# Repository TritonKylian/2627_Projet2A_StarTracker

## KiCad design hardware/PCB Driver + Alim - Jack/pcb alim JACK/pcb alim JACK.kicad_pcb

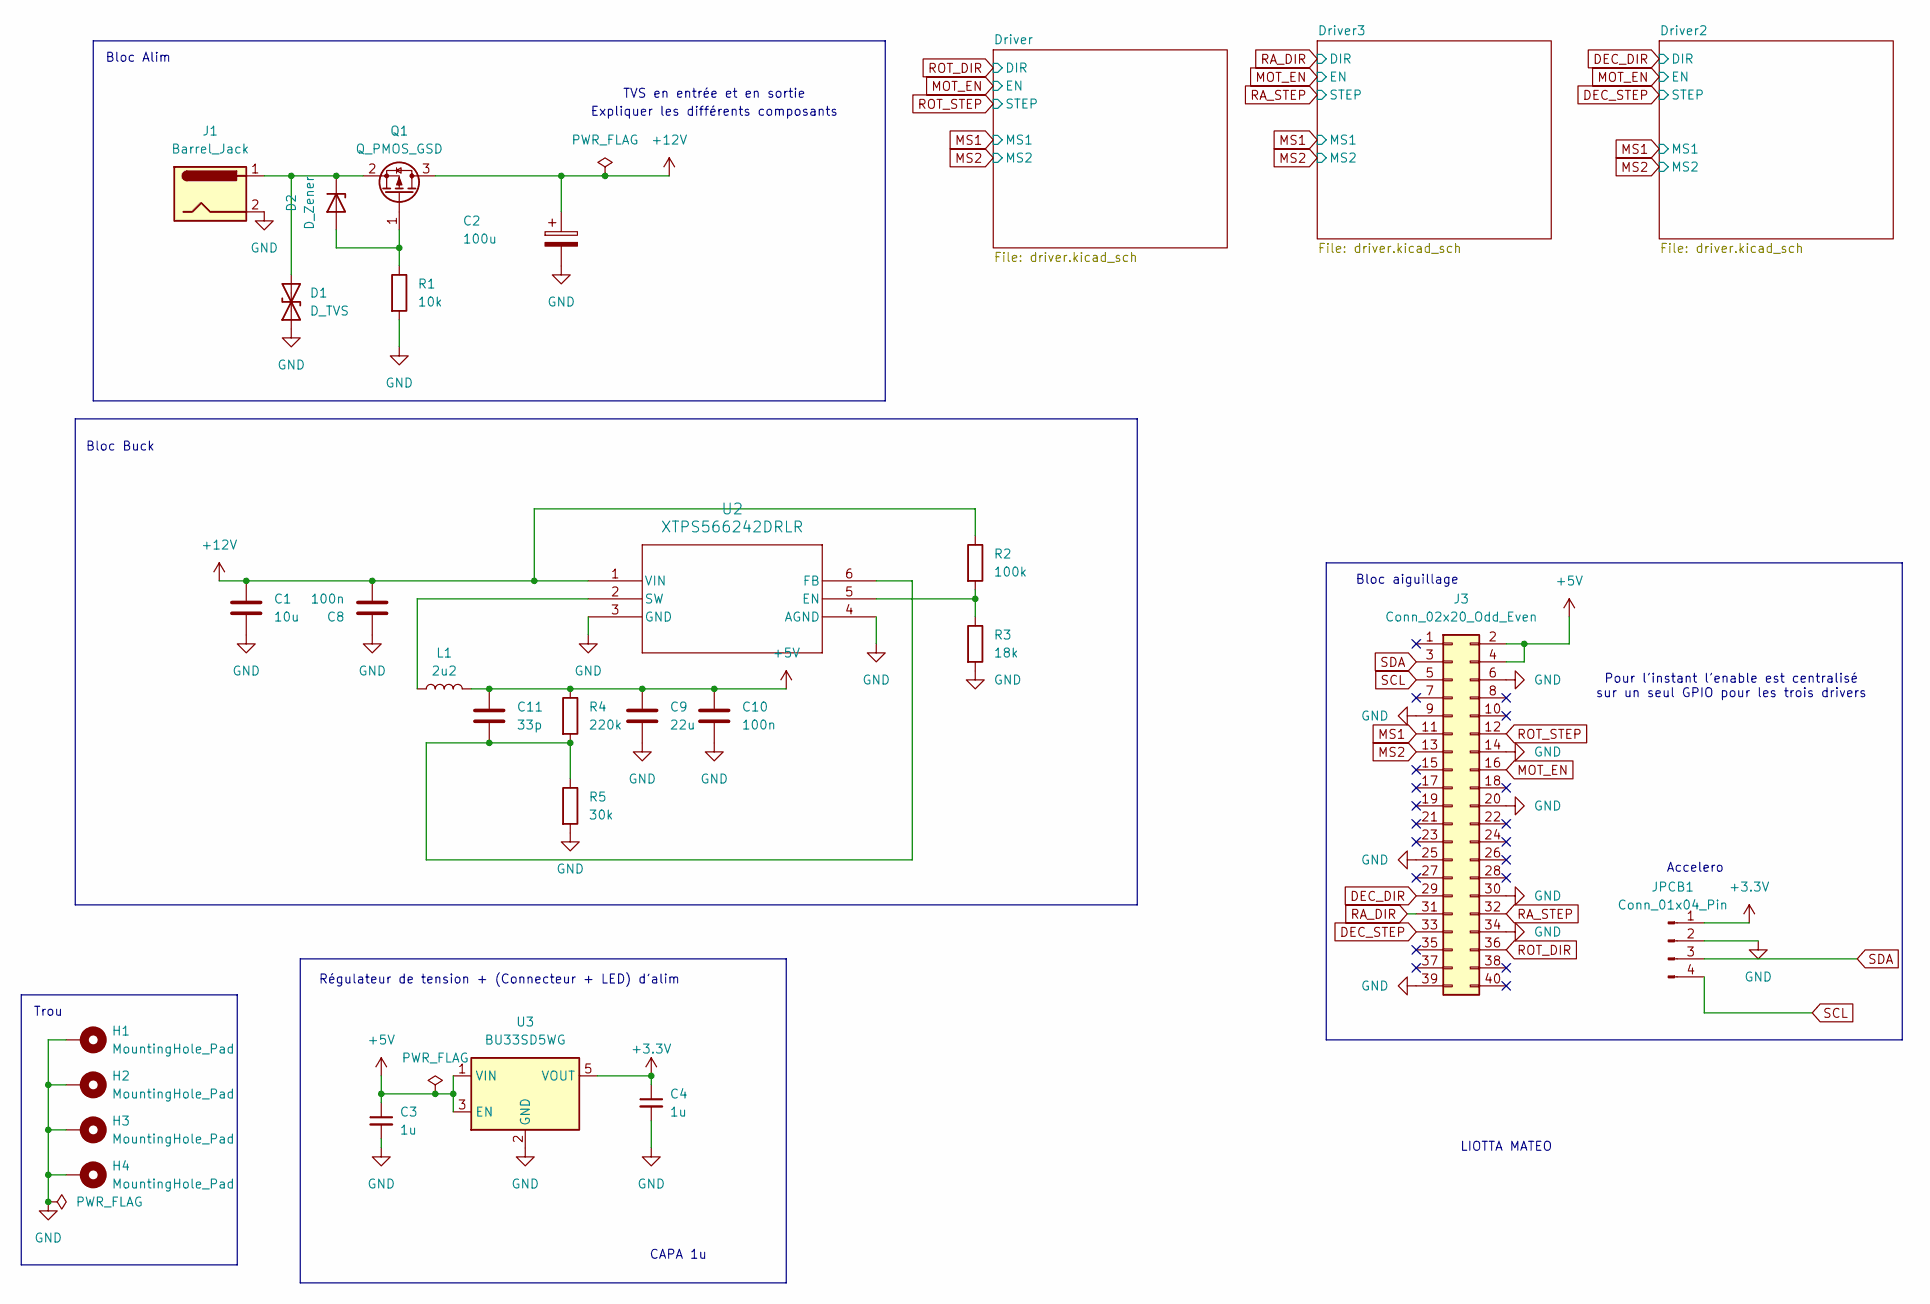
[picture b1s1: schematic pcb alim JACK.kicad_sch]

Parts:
C1: 10u; C_0805_2012Metric
C2: 100u; CP_Elec_6.3x7.7
C3, C4: 1u; C_0805_2012Metric_Pad1.18x1.45mm_HandSolder
C8, C10: 100n; C_0603_1608Metric
C9: 22u; C_0805_2012Metric
C11: 33p; C_0603_1608Metric
D1: D_TVS; D_SMB
D2: D_Zener; D_DO-35_SOD27_P7.62mm_Horizontal
H1, H2, H3, H4: MountingHole_Pad; MountingHole_2.7mm_M2.5_Pad
J1: Barrel_Jack; BarrelJack_CUI_PJ-102AH_Horizontal
J3: Conn_02x20_Odd_Even; PinSocket_2x20_P2.54mm_Vertical
JPCB1: Conn_01x04_Pin; PinHeader_1x04_P2.54mm_Vertical
L1: 2u2; L_Wuerth_WE-PD-Typ-7345; MPN 744777002
Q1: Q_PMOS_GSD; TO-263-2
R1: 10k; R_1206_3216Metric_Pad1.30x1.75mm_HandSolder
R2: 100k; R_0603_1608Metric
R3: 18k; R_0603_1608Metric
R4: 220k; R_0603_1608Metric
R5: 30k; R_0603_1608Metric
U2: XTPS566242DRLR; SOT-563
U3: BU33SD5WG; SOT-23-5

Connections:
+3.3V: C4.1, JPCB1.1, U3.5 (VOUT); also elsewhere on the board
+5V: C3.1, C9.1, C10.1, C11.1, J3.2, J3.4, L1.2, R4.1, U3.1 (VIN), U3.3 (EN)
+12V: C1.1, C2.1, C8.1, Q1.3 (D), R2.1, U2.1 (VIN); also elsewhere on the board
DEC_DIR: J3.29; also elsewhere on the board
DEC_STEP: J3.33; also elsewhere on the board
GND: C1.2, C2.2, C3.2, C4.2, C8.2, C9.2, C10.2, D1.1 (A1), H1.1 (1_1), H2.1 (1_1), H3.1 (1_1), H4.1 (1_1), J1.2, J3.6, J3.9, J3.14, J3.20, J3.25, J3.30, J3.34, J3.39, JPCB1.2, R1.2, R3.2, R5.2, U2.3 (GND), U2.4 (AGND), U3.2 (GND); also elsewhere on the board
MOT_EN: J3.16; also elsewhere on the board
MS1: J3.11; also elsewhere on the board
MS2: J3.13; also elsewhere on the board
unnamed: D1.2 (A2), D2.1 (K), J1.1, Q1.2 (S)
unnamed: D2.2 (A), Q1.1 (G), R1.1
unnamed: R2.2, R3.1, U2.5 (EN)
unnamed: C11.2, R4.2, R5.1, U2.6 (FB)
unnamed: L1.1, U2.2 (SW)
RA_DIR: J3.31; also elsewhere on the board
RA_STEP: J3.32; also elsewhere on the board
ROT_DIR: J3.36; also elsewhere on the board
ROT_STEP: J3.12; also elsewhere on the board
SCL: J3.5, JPCB1.4
SDA: J3.3, JPCB1.3

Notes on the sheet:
CAPA 1u
Accelero
Pour l'instant l'enable est centralisé sur un seul GPIO pour les trois drivers
Trou
Régulateur de tension + (Connecteur + LED) d'alim
Expliquer les différents composants
Bloc aiguillage
Bloc Buck
LIOTTA MATEO
Bloc Alim
TVS en entrée et en sortie

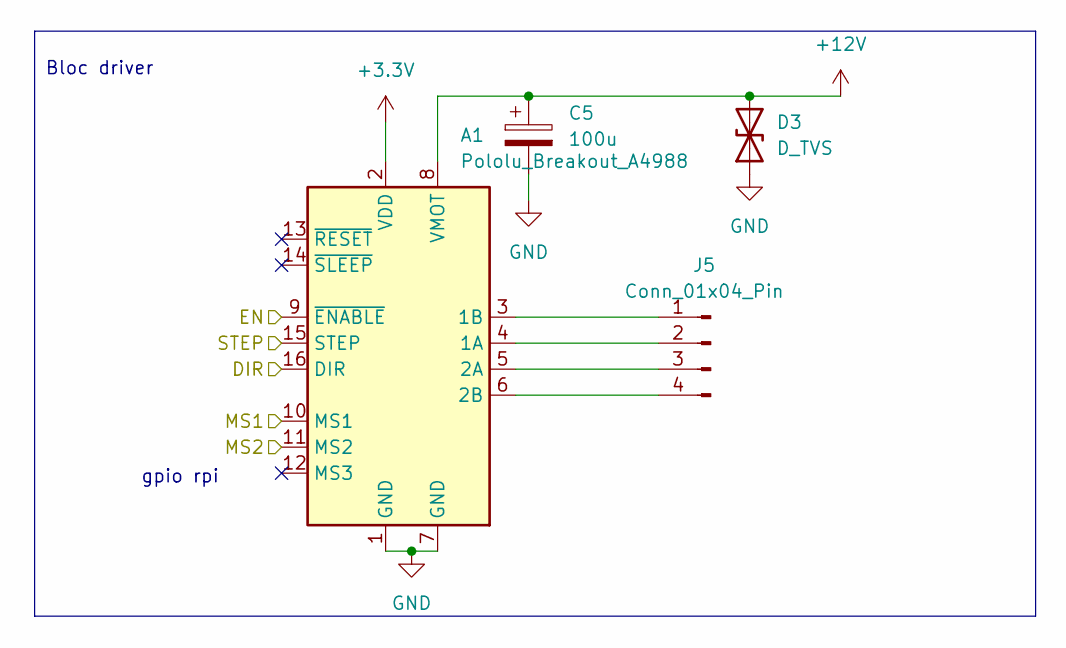
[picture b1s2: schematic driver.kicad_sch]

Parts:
A1: Pololu_Breakout_A4988; Pololu_Breakout-16_15.2x20.3mm
C5: 100u; CP_Elec_6.3x7.7
D3: D_TVS; D_SMB
J5: Conn_01x04_Pin; PinHeader_1x04_P2.54mm_Vertical

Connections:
+3.3V: A1.2 (VDD); also elsewhere on the board
+12V: A1.8 (VMOT), C5.1, D3.2 (A2); also elsewhere on the board
GND: A1.1 (GND), A1.7 (GND), C5.2, D3.1 (A1); also elsewhere on the board
MOT_EN: A1.9 (~ENABLE); also elsewhere on the board
MS1: A1.10 (MS1); also elsewhere on the board
MS2: A1.11 (MS2); also elsewhere on the board
unnamed: A1.4 (1A), J5.2
unnamed: A1.3 (1B), J5.1
unnamed: A1.5 (2A), J5.3
unnamed: A1.6 (2B), J5.4
ROT_DIR: A1.16 (DIR); also elsewhere on the board
ROT_STEP: A1.15 (STEP); also elsewhere on the board

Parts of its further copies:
A2, A3: Pololu_Breakout_A4988; Pololu_Breakout-16_15.2x20.3mm
C6, C7: 100u; CP_Elec_6.3x7.7
D4, D5: D_TVS; D_SMB
J6, J7: Conn_01x04_Pin; PinHeader_1x04_P2.54mm_Vertical

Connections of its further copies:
+3.3V: A2.2 (VDD), A3.2 (VDD); also elsewhere on the board
+12V: A2.8 (VMOT), A3.8 (VMOT), C6.1, C7.1, D4.2 (A2), D5.2 (A2); also elsewhere on the board
DEC_DIR: A2.16 (DIR); also elsewhere on the board
DEC_STEP: A2.15 (STEP); also elsewhere on the board
GND: A2.1 (GND), A2.7 (GND), A3.1 (GND), A3.7 (GND), C6.2, C7.2, D4.1 (A1), D5.1 (A1); also elsewhere on the board
MOT_EN: A2.9 (~ENABLE), A3.9 (~ENABLE); also elsewhere on the board
MS1: A2.10 (MS1), A3.10 (MS1); also elsewhere on the board
MS2: A2.11 (MS2), A3.11 (MS2); also elsewhere on the board
unnamed: A2.4 (1A), J6.2
unnamed: A2.3 (1B), J6.1
unnamed: A2.5 (2A), J6.3
unnamed: A2.6 (2B), J6.4
unnamed: A3.4 (1A), J7.2
unnamed: A3.3 (1B), J7.1
unnamed: A3.5 (2A), J7.3
unnamed: A3.6 (2B), J7.4
RA_DIR: A3.16 (DIR); also elsewhere on the board
RA_STEP: A3.15 (STEP); also elsewhere on the board

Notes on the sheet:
gpio rpi
Bloc driver

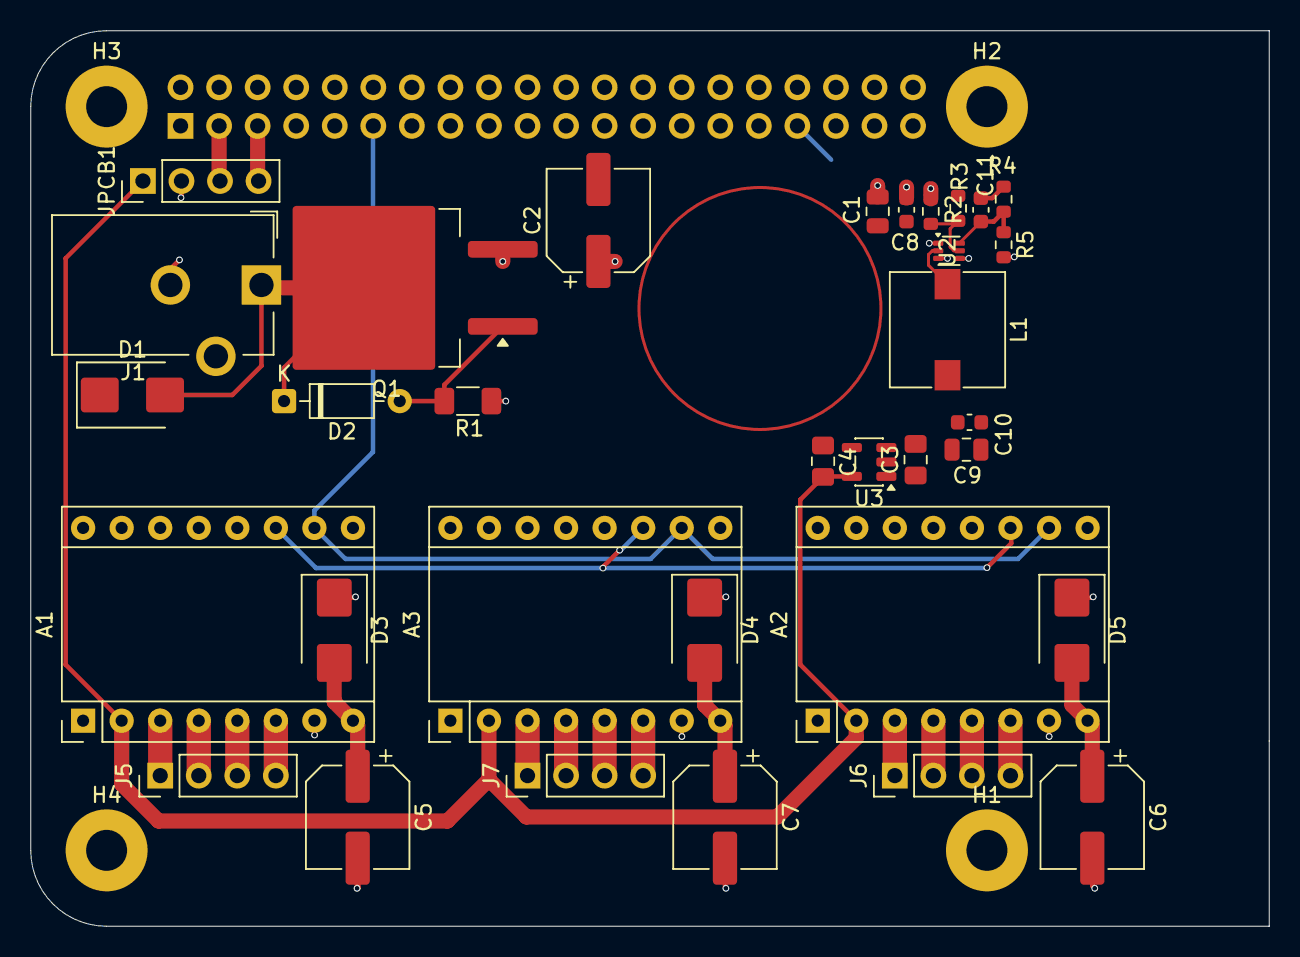
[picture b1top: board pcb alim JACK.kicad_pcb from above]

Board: 4 copper layers, 81.6 x 59.0 mm, 38 parts (1 on the bottom side), 32 nets.

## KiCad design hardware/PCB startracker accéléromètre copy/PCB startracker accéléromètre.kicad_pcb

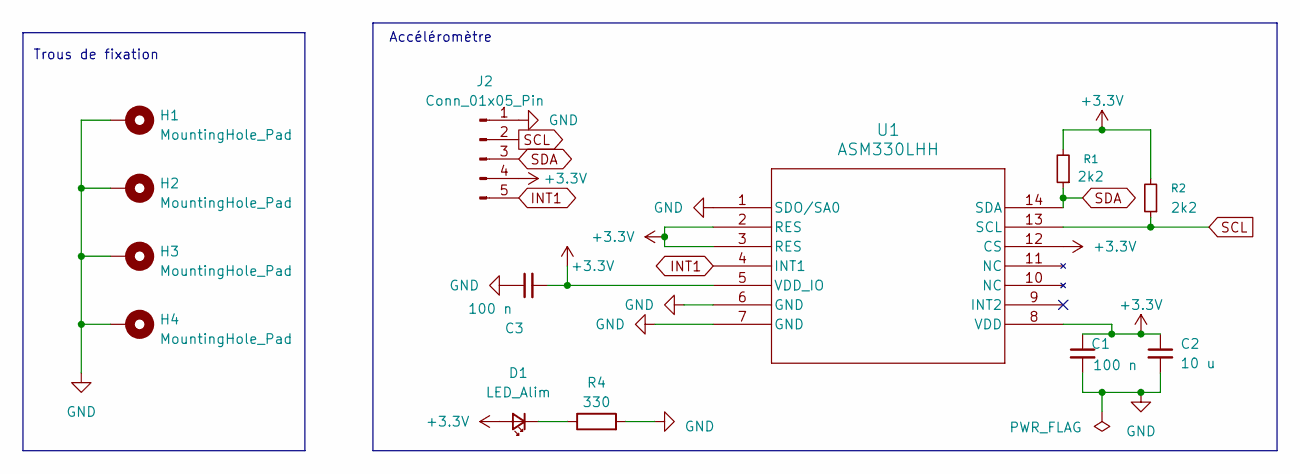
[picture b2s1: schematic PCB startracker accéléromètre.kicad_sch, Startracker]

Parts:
C1, C3: 100 n; C_0805_2012Metric
C2: 10 u; C_1206_3216Metric
D1: LED_Alim; D_0603_1608Metric_Pad1.05x0.95mm_HandSolder
H1, H2, H3, H4: MountingHole_Pad; MountingHole_3.2mm_M3_DIN965_Pad
J2: Conn_01x05_Pin; JST_PH_B5B-PH-K_1x05_P2.00mm_Vertical
R1, R2: 2k2; R_0805_2012Metric
R4: 330; R_0603_1608Metric_Pad0.98x0.95mm_HandSolder
U1: ASM330LHH; LGA-14L_2P5X3X0P83_STM

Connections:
+3.3V: C1.1, C2.1, C3.2, D1.2 (A), J2.4, R1.2, R2.2, U1.2 (RES), U1.3 (RES), U1.5 (VDD_IO), U1.8 (VDD), U1.12 (CS)
GND: C1.2, C2.2, C3.1, H1.1, H2.1, H3.1, H4.1, J2.1, R4.2, U1.1 (SDO/SA0), U1.6 (GND), U1.7 (GND)
INT1: J2.5, U1.4 (INT1)
unnamed: D1.1 (K), R4.1
SCL: J2.2, R2.1, U1.13 (SCL)
SDA: J2.3, R1.1, U1.14 (SDA)

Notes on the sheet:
Trous de fixation
Accéléromètre

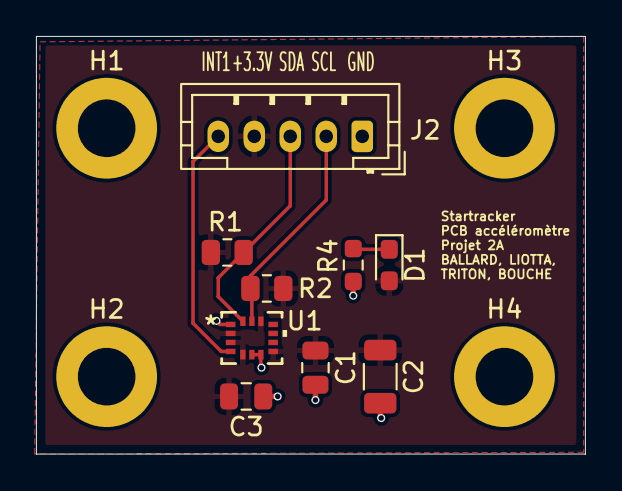
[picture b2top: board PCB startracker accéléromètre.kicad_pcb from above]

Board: 2 copper layers, 30.5 x 23.2 mm, 13 parts (0 on the bottom side), 6 nets.
